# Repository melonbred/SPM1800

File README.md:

# SPM1800
This is a PCB for a southpaw mini 1800 layout keyboard with the following features:

- Big bar and split bar support
- MX or Alps style switches
- Two independent rotary encoders
- USB Type-C
- Breakout pins for RGB underglow
- Breakout pin for USB shield ground

## WARNING
This PCB has been tested for functionality. However, please review the project files prior to placing an order for manufacturing. Users should be warned that they are manufacturing this at their own risk. 

## Layout

[KLE](http://www.keyboard-layout-editor.com/#/gists/ef914cc294dadcf20cfa8c7b7239d802)

## PCB

## BOM

| Designator | Description | Package | QTY | LCSC Part Number |
|-----------|-----------|-------|-----|-----------------|
|C1, C2, C3, C4|Capacitor - 0.1uF|0805|4|C28233|
|C5|Capacitor - 10uF|0805|1|C15850|
|C6, C7|Capacitor - 22pF|0805|2|C1804|
|C8|Capacitor - 1uF|0805|1|C28323|
|D1 - D58|Diode - 1N4148|SOD-123|58|C466653|
|D59|ESD Protection Diode - PRTR5V0U2X|SOD-143B|1|C12333|
|F1|Fuse 24V - 500mA|1206|1|C70076|
|R1, R2|Resistor - 10k|0805|2|C17414|
|R3, R4|Resistor - 5.1k|0805|2|C27834|
|R5, R6|Resistor - 22|0805|2|C17561|
|U1|Atmega32u4|QFP-44_10x10mm_P0.8mm|1|C44854|
|USB1|HRO-TYPE-C-31-M-12|HRO-TYPE-C-31-M-12|1|C165948|
|Y1|Crystal 16Mhz 3.2x2.5mm, 4 pad|3225|1|C156247|

## QMK Firmware
Firmware has been written but not tested at this time. QMK files can be found [here](https://github.com/melonbred/SPM1800/tree/master/QMK).

## Additional Notes
This project uses KiCAD libraries maintained by ai03:

- [MX_Alps_Hybrid](https://github.com/ai03-2725/MX_Alps_Hybrid)
- [random-keyboard-parts.pretty](https://github.com/ai03-2725/random-keyboard-parts.pretty)
- [Type-C.pretty](https://github.com/ai03-2725/Type-C.pretty)

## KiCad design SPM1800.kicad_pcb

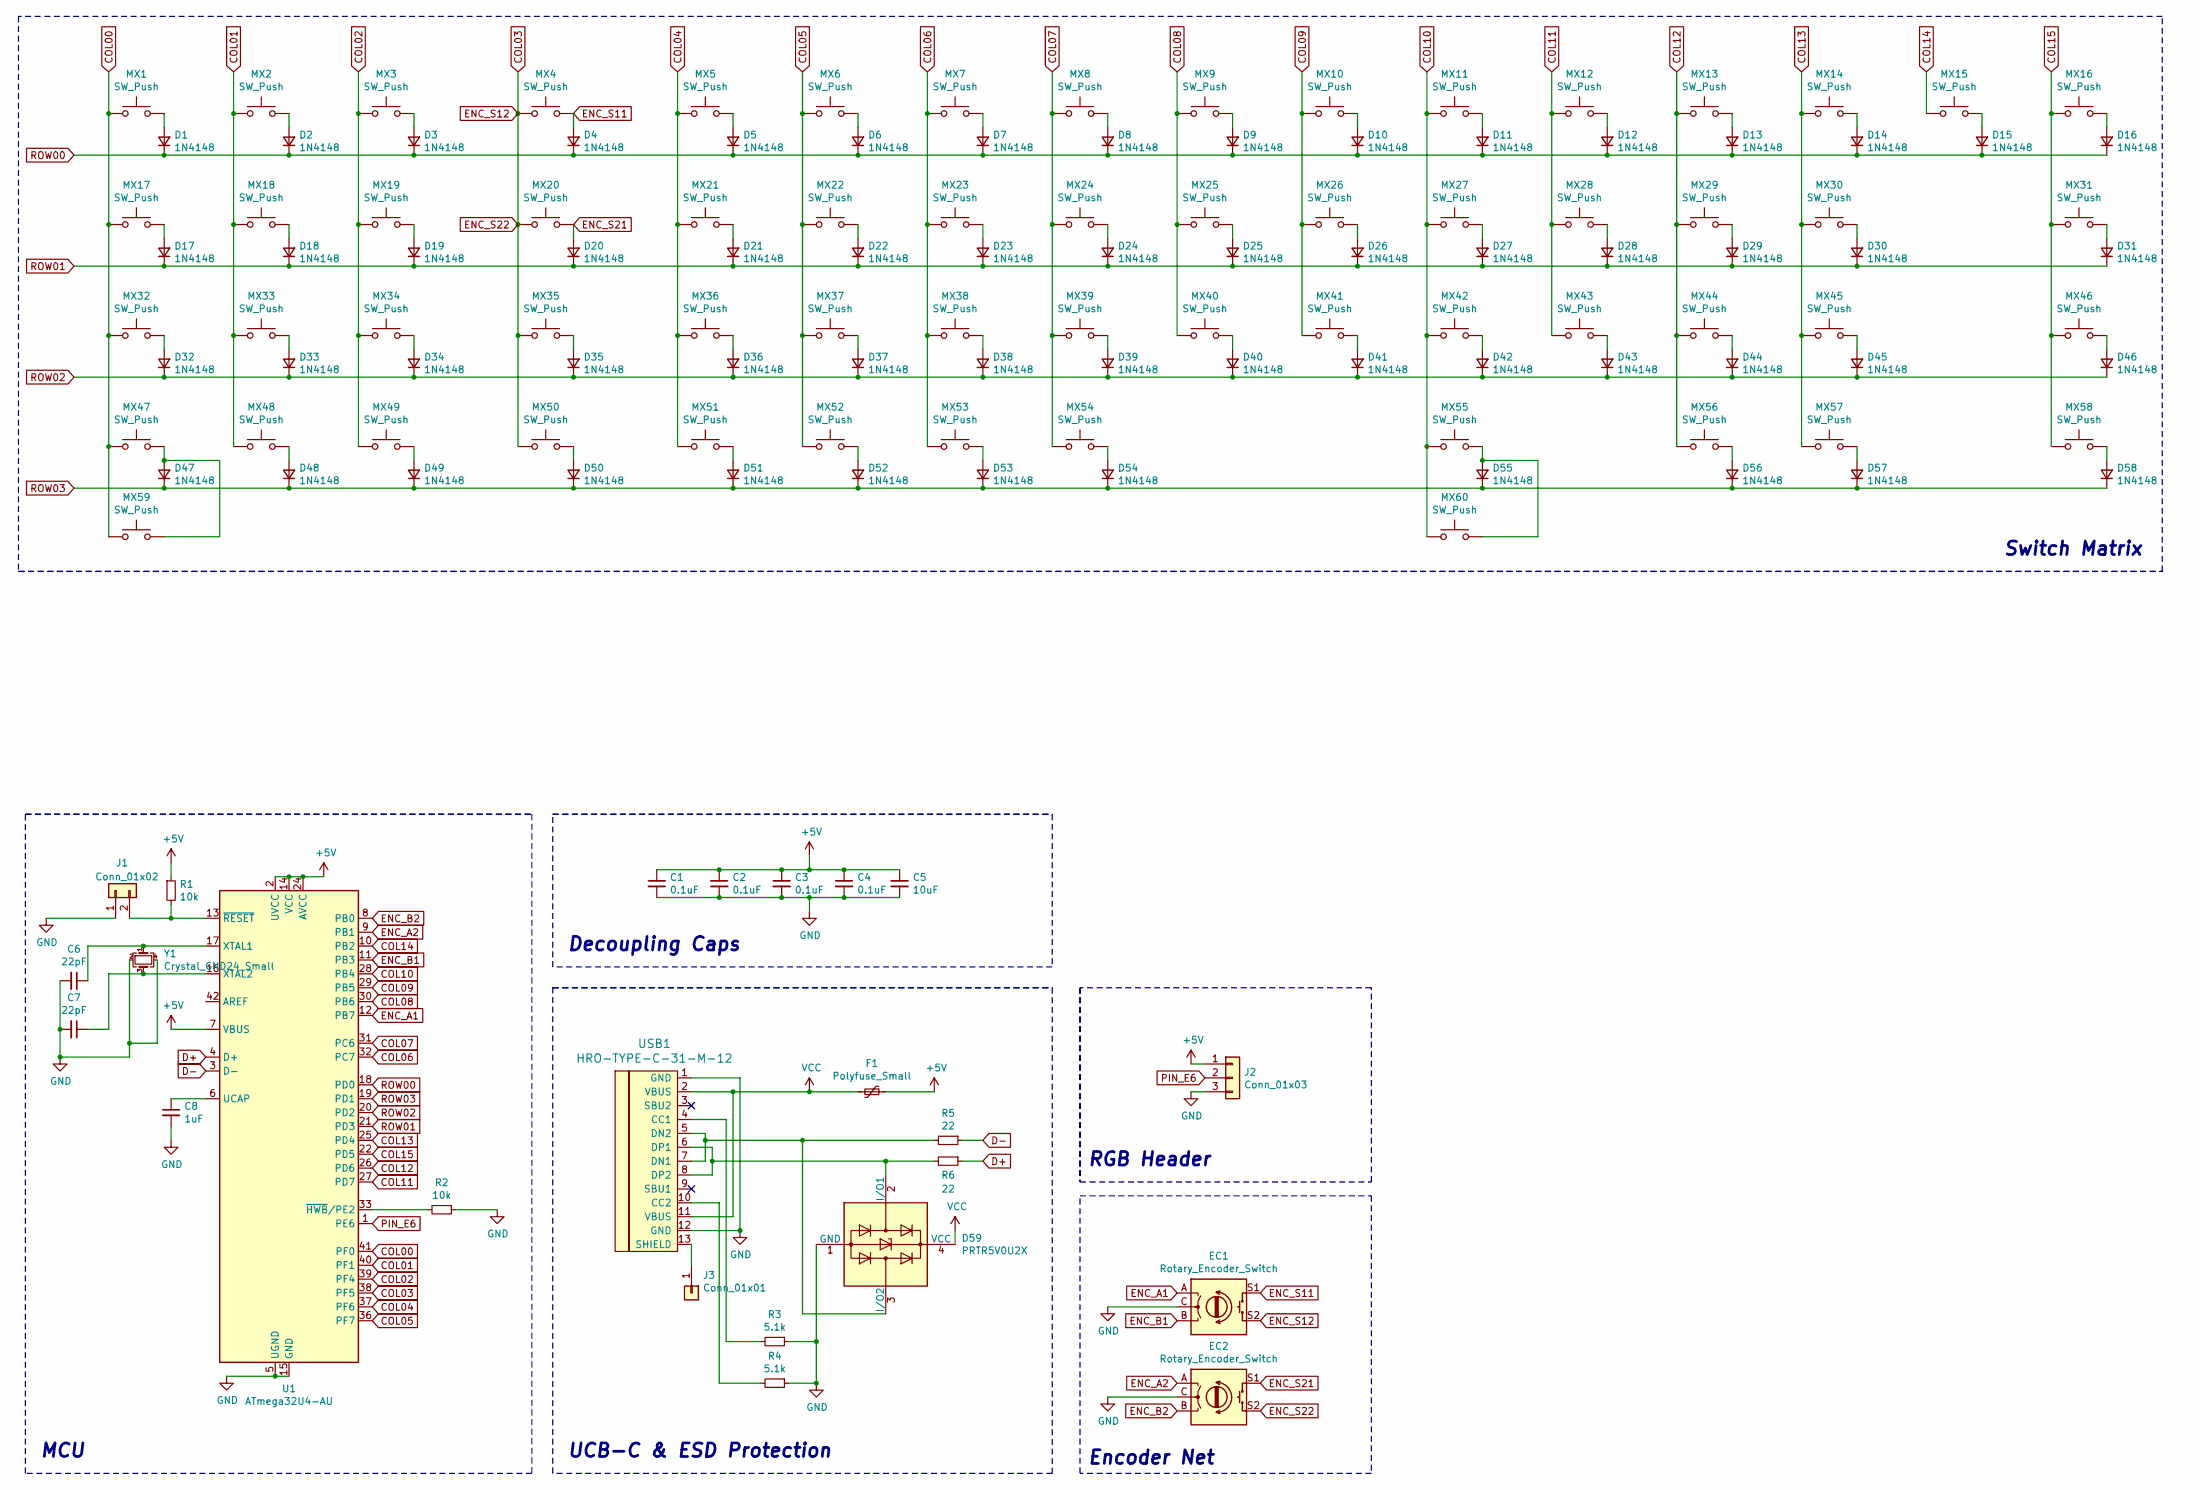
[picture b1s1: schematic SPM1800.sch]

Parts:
C1, C2, C3, C4: 0.1uF; C_0805_2012Metric
C5: 10uF; C_0805_2012Metric
C6, C7: 22pF; C_0805_2012Metric
C8: 1uF; C_0805_2012Metric
D1, D2, D3, D4, D5, D6, D7, D8, D9, D10, D11, D12, D13, D14, D15, D16, D17, D18, D19, D20, D21, D22, D23, D24, D25, D26, D27, D28, D29, D30, D31, D32, D33, D34, D35, D36, D37, D38, D39, D40, D41, D42, D43, D44, D45, D46, D47, D48, D49, D50, D51, D52, D53, D54, D55, D56, D57, D58: 1N4148; D_SOD-123
D59: PRTR5V0U2X; SOT143B
EC1, EC2: Rotary_Encoder_Switch; RotaryEncoder_Alps_EC11E-Switch_Vertical_H20mm
F1: Polyfuse_Small; Fuse_1206_3216Metric
J1: Conn_01x02; PinHeader_1x02_P2.54mm_Vertical
J2: Conn_01x03; PinHeader_1x03_P2.54mm_Vertical
J3: Conn_01x01; PinHeader_1x01_P2.54mm_Vertical
MX1, MX2, MX3, MX4, MX5, MX6, MX7, MX8, MX9, MX10, MX11, MX12, MX13, MX14, MX15, MX16, MX17, MX18, MX19, MX20, MX22, MX23, MX24, MX25, MX26, MX27, MX28, MX29, MX30, MX32, MX33, MX34, MX35, MX37, MX38, MX39, MX40, MX41, MX42, MX43, MX44, MX45, MX47, MX48, MX49, MX50, MX51, MX57: SW_Push; MX-1U-NoLED
MX21, MX46, MX52, MX53, MX56, MX58: SW_Push; MX-1.25U-NoLED
MX31, MX36: SW_Push; MX-1.75U-NoLED
MX54: SW_Push; MX-2.25U-ReversedStabilizers-NoLED
MX55: SW_Push; MX-2.75U-ReversedStabilizers-NoLED
MX59: SW_Push; MX-2U-ReversedStabilizers-NoLED
MX60: SW_Push; MX-6.25U-ReversedStabilizers-NoLED
R1, R2: 10k; R_0805_2012Metric
R3, R4: 5.1k; R_0805_2012Metric
R5, R6: 22; R_0805_2012Metric
U1: ATmega32U4-AU; TQFP-44_10x10mm_P0.8mm
USB1: HRO-TYPE-C-31-M-12; HRO-TYPE-C-31-M-12-HandSoldering
Y1: Crystal_GND24_Small; Crystal_SMD_3225-4Pin_3.2x2.5mm

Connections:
+5V: C1.1, C2.1, C3.1, C4.1, C5.1, F1.1, J2.1, R1.1, U1.2 (UVCC), U1.7 (VBUS), U1.14 (VCC), U1.24 (AVCC), U1.34 (VCC), U1.44 (AVCC)
COL00: MX1.1, MX17.1, MX32.1, MX47.1, MX59.1, U1.41 (PF0)
COL01: MX2.1, MX18.1, MX33.1, MX48.1, U1.40 (PF1)
COL02: MX3.1, MX19.1, MX34.1, MX49.1, U1.39 (PF4)
COL03: EC1.S2, EC2.S2, MX4.1, MX20.1, MX35.1, MX50.1, U1.38 (PF5)
COL04: MX5.1, MX21.1, MX36.1, MX51.1, U1.37 (PF6)
COL05: MX6.1, MX22.1, MX37.1, MX52.1, U1.36 (PF7)
COL06: MX7.1, MX23.1, MX38.1, MX53.1, U1.32 (PC7)
COL07: MX8.1, MX24.1, MX39.1, MX54.1, U1.31 (PC6)
COL08: MX9.1, MX25.1, MX40.1, U1.30 (PB6)
COL09: MX10.1, MX26.1, MX41.1, U1.29 (PB5)
COL10: MX11.1, MX27.1, MX42.1, MX55.1, MX60.1, U1.28 (PB4)
COL11: MX12.1, MX28.1, MX43.1, U1.27 (PD7)
COL12: MX13.1, MX29.1, MX44.1, MX56.1, U1.26 (PD6)
COL13: MX14.1, MX30.1, MX45.1, MX57.1, U1.25 (PD4)
COL14: MX15.1, U1.10 (PB2)
COL15: MX16.1, MX31.1, MX46.1, MX58.1, U1.22 (PD5)
D+: R6.1, U1.4 (D+)
D-: R5.1, U1.3 (D-)
ENC_A1: EC1.A, U1.12 (PB7)
ENC_A2: EC2.A, U1.9 (PB1)
ENC_B1: EC1.B, U1.11 (PB3)
ENC_B2: EC2.B, U1.8 (PB0)
ENC_S11: D4.2 (A), EC1.S1, MX4.2
ENC_S21: D20.2 (A), EC2.S1, MX20.2
GND: C1.2, C2.2, C3.2, C4.2, C5.2, C6.2, C7.2, C8.2, D59.1 (GND), EC1.C, EC2.C, J1.1, J2.3, R2.1, R3.1, R4.1, U1.5 (UGND), U1.15 (GND), U1.23 (GND), U1.35 (GND), U1.43 (GND), USB1.1 (GND), USB1.12 (GND), Y1.2, Y1.4
unnamed: C6.1, U1.17 (XTAL1), Y1.1
unnamed: C7.1, U1.16 (XTAL2), Y1.3
unnamed: C8.1, U1.6 (UCAP)
unnamed: D1.2 (A), MX1.2
unnamed: D2.2 (A), MX2.2
unnamed: D3.2 (A), MX3.2
unnamed: D5.2 (A), MX5.2
unnamed: D6.2 (A), MX6.2
unnamed: D7.2 (A), MX7.2
unnamed: D8.2 (A), MX8.2
unnamed: D9.2 (A), MX9.2
unnamed: D10.2 (A), MX10.2
unnamed: D11.2 (A), MX11.2
unnamed: D12.2 (A), MX12.2
unnamed: D13.2 (A), MX13.2
unnamed: D14.2 (A), MX14.2
unnamed: D15.2 (A), MX15.2
unnamed: D16.2 (A), MX16.2
unnamed: D17.2 (A), MX17.2
unnamed: D18.2 (A), MX18.2
unnamed: D19.2 (A), MX19.2
unnamed: D21.2 (A), MX21.2
unnamed: D22.2 (A), MX22.2
unnamed: D23.2 (A), MX23.2
unnamed: D24.2 (A), MX24.2
unnamed: D25.2 (A), MX25.2
unnamed: D26.2 (A), MX26.2
unnamed: D27.2 (A), MX27.2
unnamed: D28.2 (A), MX28.2
unnamed: D29.2 (A), MX29.2
unnamed: D30.2 (A), MX30.2
unnamed: D31.2 (A), MX31.2
unnamed: D32.2 (A), MX32.2
unnamed: D33.2 (A), MX33.2
unnamed: D34.2 (A), MX34.2
unnamed: D35.2 (A), MX35.2
unnamed: D36.2 (A), MX36.2
unnamed: D37.2 (A), MX37.2
unnamed: D38.2 (A), MX38.2
unnamed: D39.2 (A), MX39.2
unnamed: D40.2 (A), MX40.2
unnamed: D41.2 (A), MX41.2
unnamed: D42.2 (A), MX42.2
unnamed: D43.2 (A), MX43.2
unnamed: D44.2 (A), MX44.2
unnamed: D45.2 (A), MX45.2
unnamed: D46.2 (A), MX46.2
unnamed: D47.2 (A), MX47.2, MX59.2
unnamed: D48.2 (A), MX48.2
unnamed: D49.2 (A), MX49.2
unnamed: D50.2 (A), MX50.2
unnamed: D51.2 (A), MX51.2
unnamed: D52.2 (A), MX52.2
unnamed: D53.2 (A), MX53.2
unnamed: D54.2 (A), MX54.2
unnamed: D55.2 (A), MX55.2, MX60.2
unnamed: D56.2 (A), MX56.2
unnamed: D57.2 (A), MX57.2
unnamed: D58.2 (A), MX58.2
unnamed: D59.2 (I/O1), R6.2, USB1.6 (DP1), USB1.8 (DP2)
unnamed: D59.3 (I/O2), R5.2, USB1.5 (DN2), USB1.7 (DN1)
unnamed: J1.2, R1.2, U1.13 (~RESET)
unnamed: J3.1, USB1.13 (SHIELD)
unnamed: R2.2, U1.33 (~HWB~/PE2)
unnamed: R3.2, USB1.4 (CC1)
unnamed: R4.2, USB1.10 (CC2)
PIN_E6: J2.2, U1.1 (PE6)
ROW00: D1.1 (K), D2.1 (K), D3.1 (K), D4.1 (K), D5.1 (K), D6.1 (K), D7.1 (K), D8.1 (K), D9.1 (K), D10.1 (K), D11.1 (K), D12.1 (K), D13.1 (K), D14.1 (K), D15.1 (K), D16.1 (K), U1.18 (PD0)
ROW01: D17.1 (K), D18.1 (K), D19.1 (K), D20.1 (K), D21.1 (K), D22.1 (K), D23.1 (K), D24.1 (K), D25.1 (K), D26.1 (K), D27.1 (K), D28.1 (K), D29.1 (K), D30.1 (K), D31.1 (K), U1.21 (PD3)
ROW02: D32.1 (K), D33.1 (K), D34.1 (K), D35.1 (K), D36.1 (K), D37.1 (K), D38.1 (K), D39.1 (K), D40.1 (K), D41.1 (K), D42.1 (K), D43.1 (K), D44.1 (K), D45.1 (K), D46.1 (K), U1.20 (PD2)
ROW03: D47.1 (K), D48.1 (K), D49.1 (K), D50.1 (K), D51.1 (K), D52.1 (K), D53.1 (K), D54.1 (K), D55.1 (K), D56.1 (K), D57.1 (K), D58.1 (K), U1.19 (PD1)
VCC: D59.4 (VCC), F1.2, USB1.2 (VBUS), USB1.11 (VBUS)

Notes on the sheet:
MCU
UCB-C & ESD Protection
Decoupling Caps
Switch Matrix
Encoder Net
RGB Header

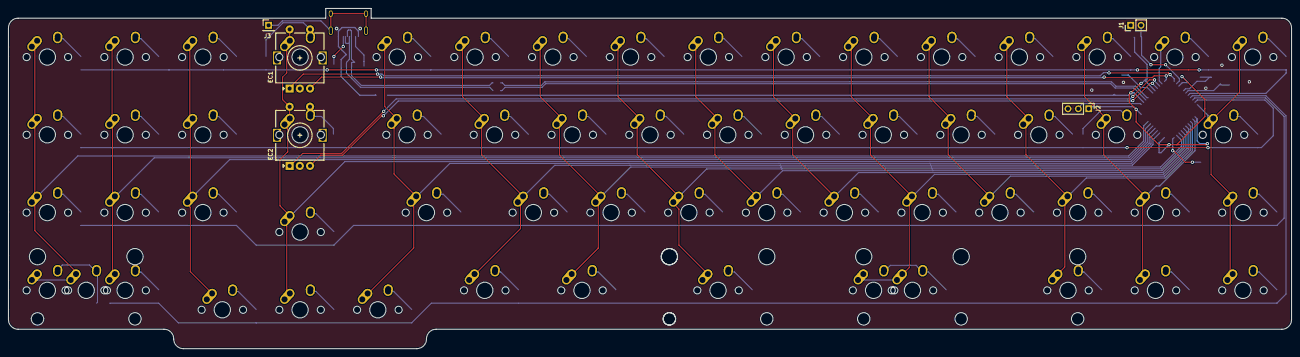
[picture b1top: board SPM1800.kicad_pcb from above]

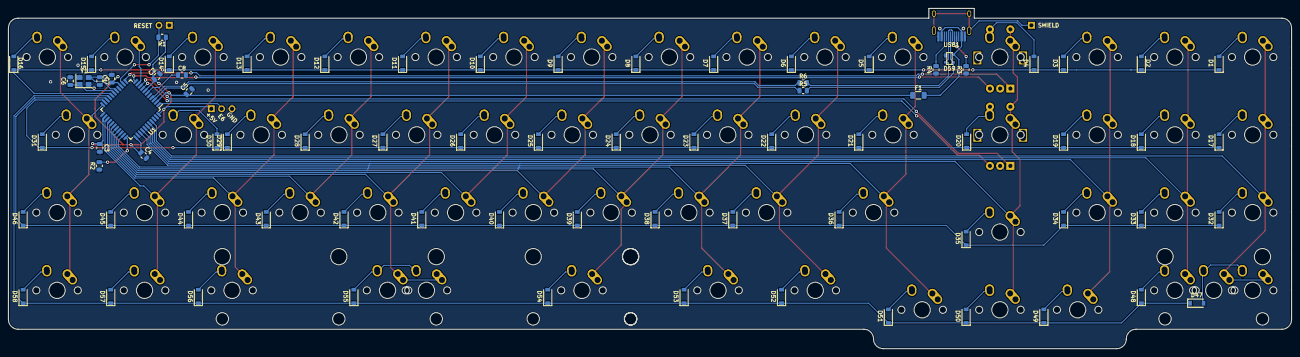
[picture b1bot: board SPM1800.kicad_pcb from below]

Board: 2 copper layers, 314.3 x 83.3 mm, 142 parts (77 on the bottom side), 98 nets.

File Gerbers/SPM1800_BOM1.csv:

"Id";"Designator";"Package";"Quantity";"Designation";"Supplier and ref";
1;"R6,R5";"R_0805_2012Metric";2;"22";;;
2;"J2";"PinHeader_1x03_P2.54mm_Vertical";1;"Conn_01x03";;;
3;"J3";"PinHeader_1x01_P2.54mm_Vertical";1;"Conn_01x01";;;
4;"C1,C4,C3,C2";"C_0805_2012Metric";4;"0.1uF";;;
5;"EC2,EC1";"RotaryEncoder_Alps_EC11E-Switch_Vertical_H20mm";2;"Rotary_Encoder_Switch";;;
6;"MX27,MX32,MX4,MX6,MX1,MX57,MX51,MX50,MX49,MX48,MX47,MX45,MX44,MX43,MX42,MX41,MX40,MX39,MX38,MX37,MX35,MX34,MX33,MX30,MX29,MX28,MX26,MX25,MX24,MX23,MX22,MX20,MX19,MX18,MX17,MX16,MX15,MX14,MX13,MX12,MX11,MX10,MX9,MX8,MX7,MX5,MX3,MX2";"MX-1U-NoLED";48;"SW_Push";;;
7;"Y1";"Crystal_SMD_3225-4Pin_3.2x2.5mm";1;"Crystal_GND24_Small";;;
8;"USB1";"HRO-TYPE-C-31-M-12-HandSoldering";1;"HRO-TYPE-C-31-M-12";;;
9;"U1";"TQFP-44_10x10mm_P0.8mm";1;"ATmega32U4-AU";;;
10;"R4,R3";"R_0805_2012Metric";2;"5.1k";;;
11;"R2,R1";"R_0805_2012Metric";2;"10k";;;
12;"MX59";"MX-2U-ReversedStabilizers-NoLED";1;"SW_Push";;;
13;"MX58,MX56,MX53,MX52,MX46,MX21";"MX-1.25U-NoLED";6;"SW_Push";;;
14;"MX55";"MX-2.75U-ReversedStabilizers-NoLED";1;"SW_Push";;;
15;"MX60";"MX-6.25U-ReversedStabilizers-NoLED";1;"SW_Push";;;
16;"MX54";"MX-2.25U-ReversedStabilizers-NoLED";1;"SW_Push";;;
17;"MX36,MX31";"MX-1.75U-NoLED";2;"SW_Push";;;
18;"J1";"PinHeader_1x02_P2.54mm_Vertical";1;"Conn_01x02";;;
19;"F1";"Fuse_1206_3216Metric";1;"Polyfuse_Small";;;
20;"D59";"SOT143B";1;"PRTR5V0U2X";;;
21;"D58,D57,D56,D55,D54,D53,D52,D51,D50,D49,D48,D47,D46,D45,D44,D43,D42,D41,D40,D39,D38,D37,D36,D35,D34,D33,D32,D31,D30,D29,D28,D27,D26,D25,D24,D23,D22,D21,D20,D19,D18,D17,D16,D15,D14,D13,D12,D11,D10,D9,D8,D7,D6,D5,D4,D3,D2,D1";"D_SOD-123";58;"1N4148";;;
22;"C8";"C_0805_2012Metric";1;"1uF";;;
23;"C7,C6";"C_0805_2012Metric";2;"22pF";;;
24;"C5";"C_0805_2012Metric";1;"10uF";;;

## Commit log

2020-11-01 Initialize
2020-11-01 Added .step model
2020-11-01 Added gerbers
2020-11-01 Updated BOM
2020-11-04 Updated PCB
    Added series resistors to data lines.
2020-11-04 Msc. Update
    PCB images updated.
    Fixed formatting
2020-11-04 Msc. Updated
    PCB images.
    Fixed formatting
2020-11-05 Updated PCB
    COL13 to D4
    COL15 to D5
2020-11-05 Added QMK fw
    alpha
2020-11-05 Update README
    Added link to QMK files.
    Spelling
2020-11-06 Updated Gerbers
2020-11-07 Prepared production files
    For prototyping
2020-11-19 STEP updated
2020-11-19 Moved STEP file
2021-02-13 Quick Fix
2021-02-13 Added kamelon pan
2021-02-27 Update BOM
